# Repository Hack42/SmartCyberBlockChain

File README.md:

# SmartCyberBlockChain
# SmartCyberBlockChain

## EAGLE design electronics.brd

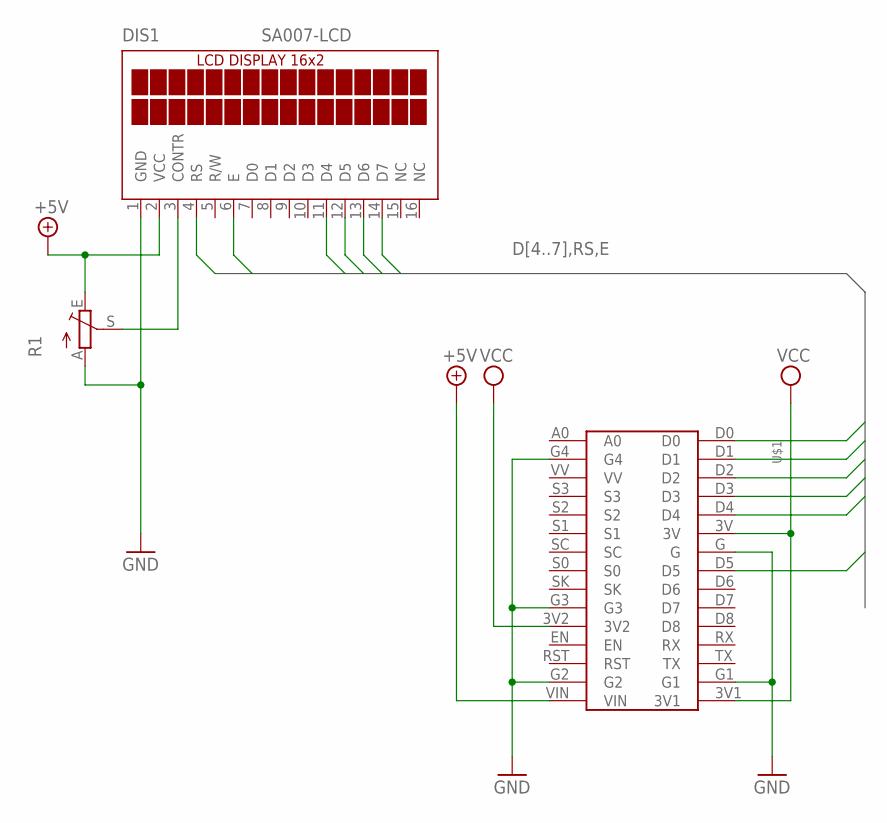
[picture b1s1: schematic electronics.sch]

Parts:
DIS1: SA007-LCD
R1: TRIM_EU-CA9H; CA9H
U$1: LOLIN

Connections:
+5V: DIS1.2 (VCC), R1.E, U$1.VIN
D4: DIS1.11 (D4), U$1.D0
D5: DIS1.12 (D5), U$1.D1
D6: DIS1.13 (D6), U$1.D2
D7: DIS1.14 (D7), U$1.D3
E: DIS1.6 (E), U$1.D5
GND: DIS1.1 (GND), R1.A, U$1.G, U$1.G1, U$1.G2, U$1.G3, U$1.G4
unnamed: DIS1.3 (CONTR), R1.S
RS: DIS1.4 (RS), U$1.D4
VCC: U$1.3V, U$1.3V1, U$1.3V2

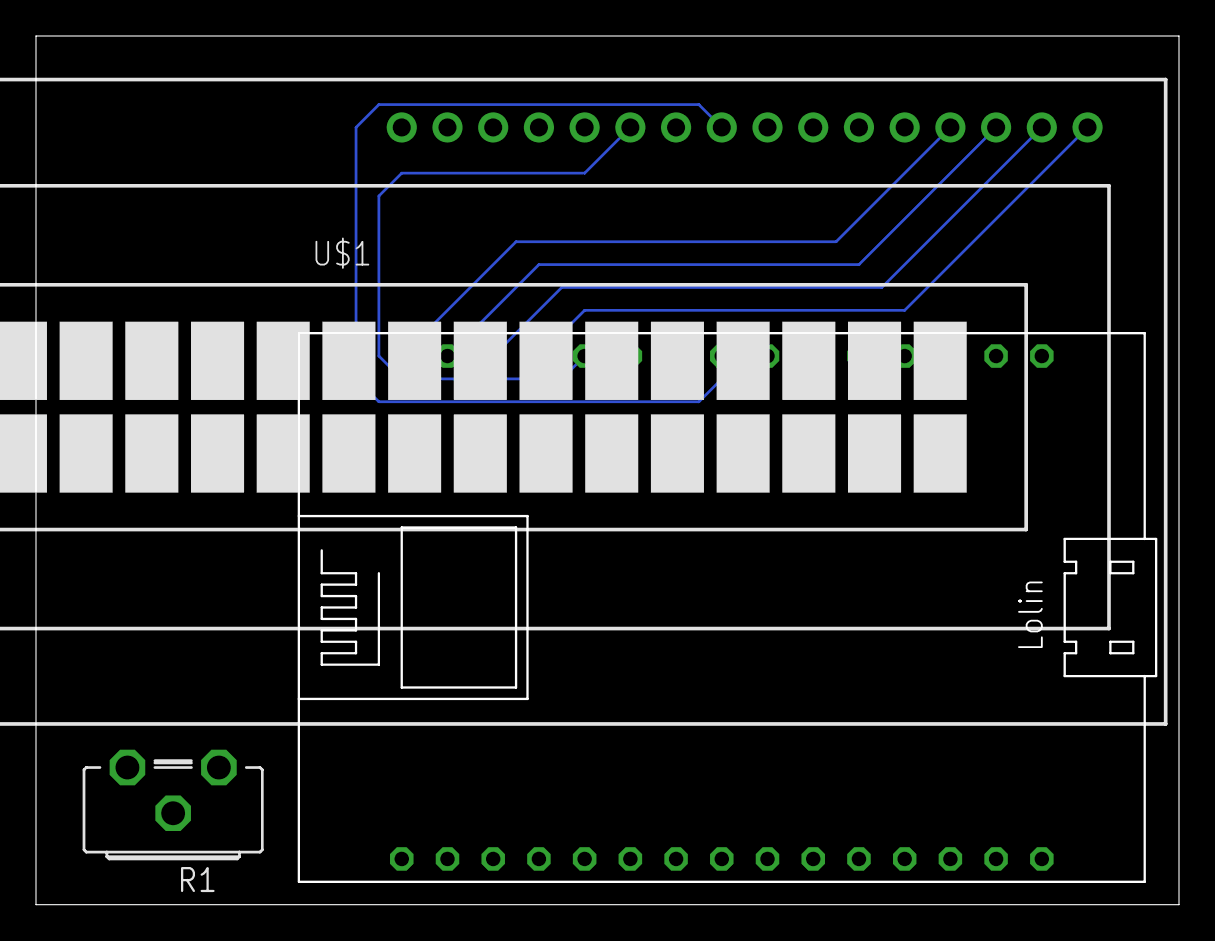
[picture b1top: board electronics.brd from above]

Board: 2 copper layers, 63.4 x 48.1 mm, 3 parts (0 on the bottom side), 10 nets.

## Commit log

2018-03-24 added files
